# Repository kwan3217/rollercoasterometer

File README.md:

# rollercoasterometer
Rollercoasterometer

## kicad7 branch
This one is based on the Shipometer 23.03, but updated to KiCad 7.0. There are initially no other changes.

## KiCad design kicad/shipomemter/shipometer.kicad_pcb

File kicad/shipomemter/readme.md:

# Shipometer
The *Shipometer* is designed to record as much data as possible on a cruise
ship. To this end, it is composed of a Raspberry Pi running Raspbian, along
with several other programs, and both off-the-shelf and custom hardware.

Sensors include:

* ADS-B radio for recording flight information
* AIS radio for recording ship logs
* GPS for own position and timing
* Inertial measurement unit because we can
* Pressure, temperature, and humidity sensor because it's interesting
* Magnetometer, which will be challenging to use on a steel ship
* Logging of on-chip die temperature, clock frequency, and load.

This folder documents the Shipometer HAT, which holds a socket for a Sparkfun
ZED-F9R breakout GPS. This part has its own inertial sensor and GPS receiver,
as well as a serial data stream and an accurate PPS signal.

We also include sockets for what I call *stamps* (based on their appearance
with castellated edges). The stamps take up much less space than a full breakout
board, but at the same time can be independently assembled and tested. I have
in mind the wild idea of a whole series of stamps, all with roughly compatible
pinouts. So far I have designed two, one which supports a BME280 
pressure/temperature/humidity sensor, and one which supports an ICM20948 9DoF
sensor.

The hat itself includes an LPC2102 microcontroller, used as a timer. It is able
to record the time of each PPS to within one 60MHz clock cycle, and is also
hooked up to time the data-ready outputs of the inertial and pressure stamp.

It also includes hardware to multiplex the chip select lines (so that all chips
can be read in SPI mode) and a 1.8V regulator, both to supply power to the timer
and to the inertial sensor.

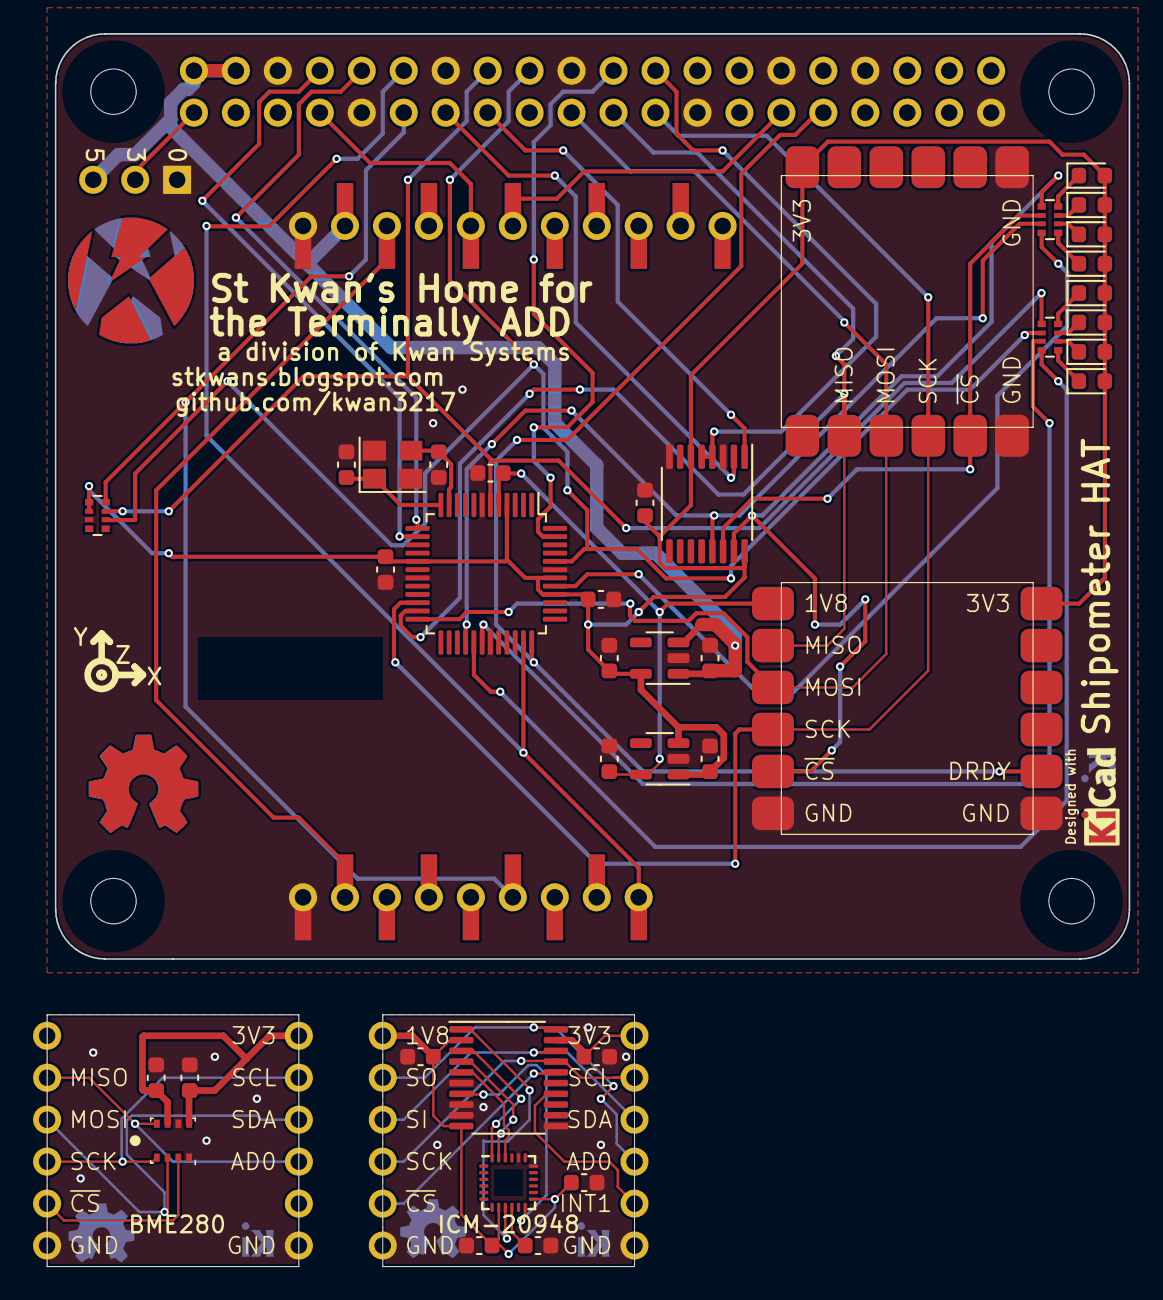
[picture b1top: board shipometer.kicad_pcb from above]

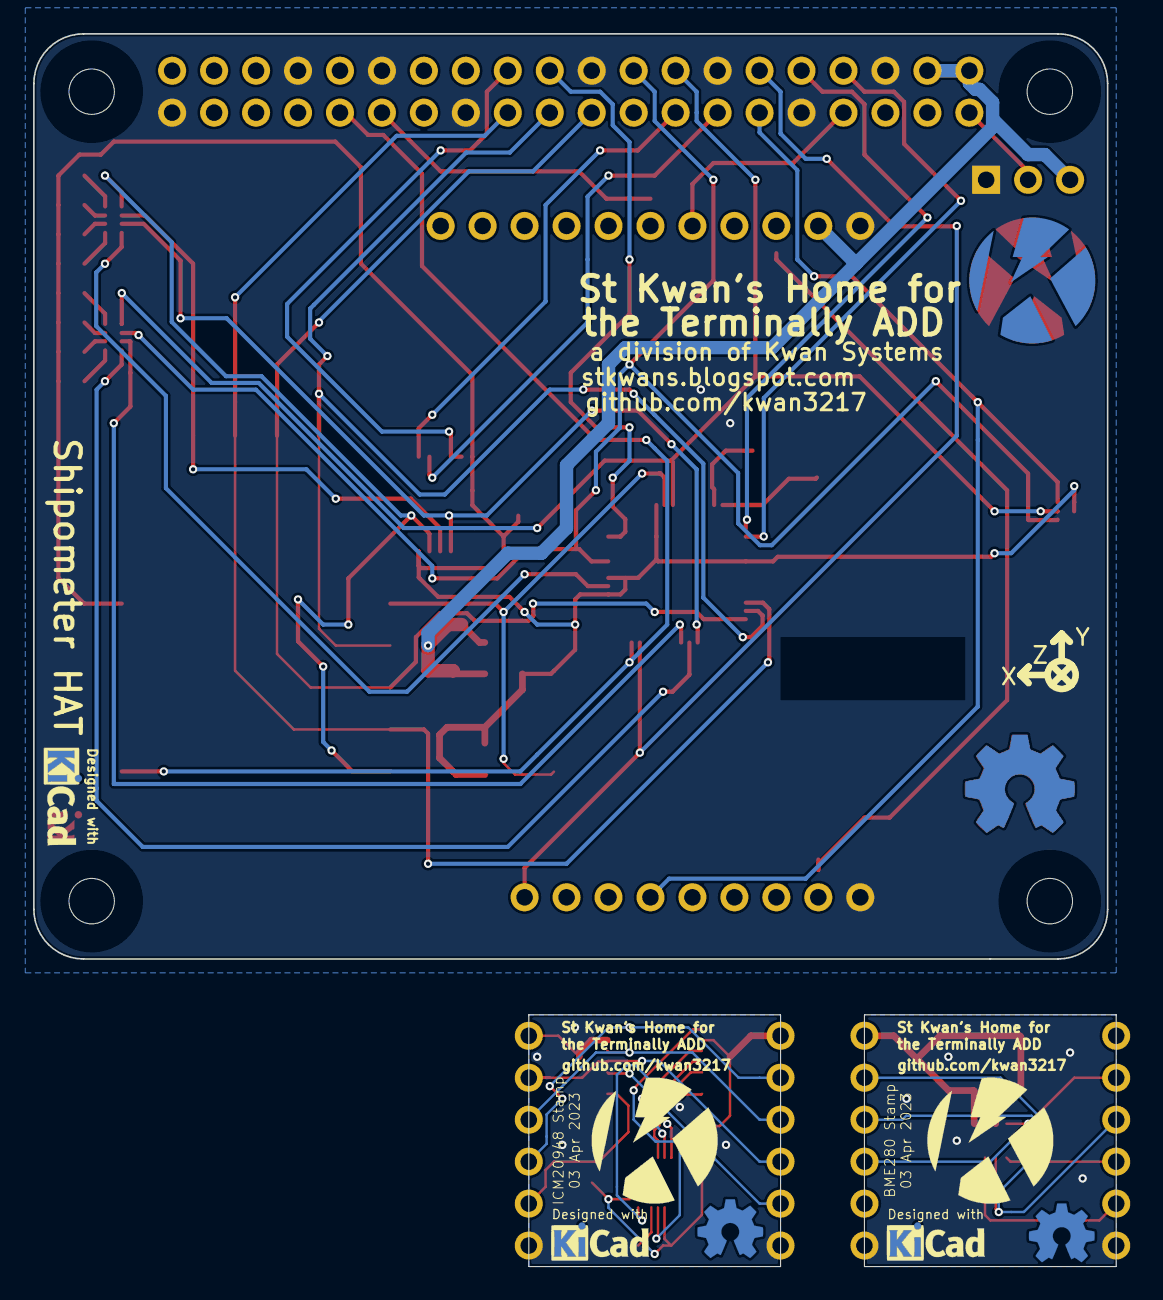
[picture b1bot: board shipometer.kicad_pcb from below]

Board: 2 copper layers, 65.5 x 74.6 mm, 56 parts (9 on the bottom side), 58 nets.

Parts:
C116, C206, C208, C401, C405, C501, C505, C605, C617, C640: 1uF; C_0603_1608Metric
C302, C308, C310, C313, C319: 100nF; C_0603_1608Metric
C611, C612: 22pF; C_0603_1608Metric
D101, D103, D104: White; LED_0603_1608Metric
D106: Blue; LED_0603_1608Metric
D129: Red; LED_0603_1608Metric
D130: Green; LED_0603_1608Metric
D141, D144: Yellow; LED_0603_1608Metric
G101: Axis
G102, G105: KwanSystems; StKwansSoldermask
G103, G107, G202, G302: Designed with; Symbol_KiCAD-Logo_CopperAndSilkScreenTop_small
G104, G106: OSHW; OSHW-Symbol_6.7x6mm_SolderMask
G201, G301: github.com/kwan3217; KWAN_CIRCLE
G203, G303: OSHW; OSHW-Symbol_4x3.6mm_SolderMask
J101: Raspberry_Pi_40; PiHAT_NoSlot_Narrow
J102: Conn_01x03; PinHeader_1x03_P2.54mm_Horizontal
J104: ICM20948; StampPad
J105: BME280; StampPad
J106: ZED-F9R
J201, J301: Stamp
R101, R102: 330; R_Array_Convex_4x0402
R103: 10k; R_Array_Convex_4x0402
U102: 74LS138; TSSOP-16_4.4x5mm_P0.65mm
U201: BME280; Bosch_LGA-8_2.5x2.5mm_P0.65mm_ClockwisePinNumbering
U301: ICM-20948; InvenSense_QFN-24_3x3mm_P0.4mm
U302: TXS0108EPW; TSSOP-20_4.4x6.5mm_P0.65mm
U401: TCR2EF 3.3V; SOT-23-5
U501: TCR2EF 1.8V; SOT-23-5
U601: LPC210x; LQFP-48_7x7mm_P0.5mm
Y601: 12MHz; Crystal_SMD_Abracon_ABM8G-4Pin_3.2x2.5mm

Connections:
3V3: J106.3 (3V3), J106.13 (3V3)
+1V8: C505.1, C605.1, J104.1 (1V8), U501.5 (OUT), U601.5 (VDD(1V8))
+3.3VP: J101.1 (3V3), J102.2
+3V3: C116.1, C405.1, C501.1, C617.1, C640.1, D101.2 (A), D103.2 (A), D104.2 (A), D106.2 (A), D129.2 (A), D130.2 (A), D141.2 (A), D144.2 (A), J104.12 (3V3), J105.12 (3V3), R103.1 (4), R103.2 (4), U102.6 (E3), U102.16 (VCC), U401.5 (OUT), U501.1 (IN), U501.3 (EN), U601.4 (VBAT), U601.17 (VDD(3V3)), U601.40 (VDD(3V3)), U601.42 (VDDA)
+5V: C401.1, J101.2 (5V), J101.4 (5V), J102.3, J106.2 (5V), U401.1 (IN), U401.3 (EN)
/BOOTSTRAP-: D144.1 (K), R102.7 (5)
/CS_A0: J101.15 (GPIO22_(GEN3)), U102.1 (A0)
/CS_A1: J101.13 (GPIO27_(GEN2)), U102.2 (A1)
/DRDY-: D129.1 (K), R102.5
/DRDY_6D: J101.31 (GPIO6), J104.8 (DRDY), U601.36 ((CTS1/CAP1.1/AD0.4)P0.11)
/DRDY_MAG: J101.22 (GPIO25_(GEN6)), U601.47 ((CAP1.2/SCL1)P0.17)
/DRDY_MAG-: D130.1 (K), R102.6 (5)
/GPS_RX: J101.7 ((TX3)_GPIO4), J106.5 (RX/MOSI)
/GPS_TX: J101.29 ((RX3)_GPIO5), J106.6 (TX/MISO)
/GPS_~RESET: J101.11 (GPIO17_(GEN0)), J106.17 (~RESET), R103.8 (5)
/IMU/INT1_1V8: U301.12 (INT1), U302.7 (A6)
/IMU/INT1_3V3: J301.8 (INT1), U302.14 (B6)
/IMU/MISO_1V8: U301.9 (SDO/AD0), U302.1 (A1)
/IMU/MISO_3V3: J301.2 (MISO), J301.9 (AD0), U302.20 (B1)
/IMU/MOSI_1V8: U301.24 (SDA/SDI), U302.3 (A2)
/IMU/MOSI_3V3: J301.3 (MOSI), J301.10 (SDA), U302.18 (B2)
/IMU/Q_1V8: C302.1, C308.1, C313.1, J301.1 (1V8), U301.8 (VDDIO), U301.13 (VDD), U302.2 (VCCA), U302.10 (OE)
/IMU/Q_3V3: C319.1, J301.12 (3V3), U302.19 (VCCB)
/IMU/Q_GND: C302.2, C308.2, C310.2, C313.2, C319.2, J301.6 (GND), J301.7 (GND), U301.18 (GND), U301.20 (GND), U302.6 (A5), U302.8 (A7), U302.9 (A8), U302.11 (GND)
/IMU/SCK_1V8: U301.23 (SCL/SCLK), U302.4 (A3)
/IMU/SCK_3V3: J301.4 (SCK), J301.11 (SCL), U302.17 (B3)
/IMU/~CS_1V8: U301.22 (~CS), U302.5 (A4)
/IMU/~CS_3V3: J301.5 (~CS), U302.16 (B4)
/LPC_RESET-: D106.1 (K), R102.8 (5)
/LPC_RX: J101.8 ((TX0)_GPIO14), U601.14 ((RXD0/MAT3.2)P0.1)
/LPC_TX: J101.10 ((RX0)_GPIO15), U601.13 ((TXD0/MAT3.1)P0.0)
/LPC_~BOOTSTRAP: J101.18 (GPIO24_(GEN5)), R102.2 (4), R103.6 (5), U601.44 ((DCD1/SCK1/EINT1)P0.14)
/LPC_~RESET: J101.16 (GPIO23_(GEN4)), R102.1 (4), R103.7 (5), U601.6 (~RST)
/MISO_3V3: J101.21 ((SPI_MISO)_GPIO9), J104.2 (MISO), J105.2 (MISO), U601.23 ((MISO0/MAT0.1)P0.5)
/MOSI_3V3: J101.19 ((SPI_MOSI)_GPIO10), J104.3 (MOSI), J105.3 (MOSI), U601.24 ((MOSI0/CAP0.2)P0.6)
/PPS: J101.12 (GPIO18_(GEN1)), J106.20 (PPS), U601.35 ((RTS1/CAP1.0/AD0.3)P0.10)
/PPS-: D141.1 (K), R101.5
/Pressure/MISO: J201.2 (MISO), J201.9 (AD0), U201.5 (SDO)
/Pressure/MOSI: J201.3 (MOSI), J201.10 (SDA), U201.3 (SDI)
/Pressure/Q_3V3: C206.1, C208.1, J201.12 (3V3), U201.6 (VDDIO), U201.8 (VDD)
/Pressure/Q_GND: C206.2, C208.2, J201.6 (GND), J201.7 (GND), U201.1 (GND), U201.7 (GND)
/Pressure/SCK: J201.4 (SCK), J201.11 (SCL), U201.4 (SCK)
/Pressure/~CS: J201.5 (~CS), U201.2 (CSB)
/SCK_3V3: J101.23 ((SPI_SCLK)_GPIO11), J104.4 (SCK), J105.4 (SCK), U601.22 ((SCK0/CAP0.1)P0.4)
/Timer/XTAL1: C611.2, U601.11 (XTAL1), Y601.3
/Timer/XTAL2: C612.2, U601.12 (XTAL2), Y601.1
/~CE0: J101.24 ((~SPI_CE0)_GPIO8), U102.4 (E1), U102.5 (E2)
/~CS_6D: J104.5 (~CS), R101.1 (4), U102.15 (O0)
/~CS_6D+: D101.1 (K), R101.8 (5)
/~CS_LPC: R101.3 (4), U102.13 (O2), U601.28 ((SSEL0/MAT2.0)P0.7)
/~CS_LPC+: D104.1 (K), R101.6 (5)
/~CS_PRES: J105.5 (~CS), R101.2 (4), U102.14 (O1)
/~CS_PRES+: D103.1 (K), R101.7 (5)
/~DRDY_6D_ECHO: R102.4, U601.29 ((TXD1/MAT2.1)P0.8)
/~DRDY_MAG_ECHO: R102.3 (4), U601.30 ((RXD1/MAT2.2)P0.9)
/~PPS_ECHO: R101.4, U601.41 ((DTR1/MAT1.1)P0.13)
GND: C116.2, C401.2, C405.2, C501.2, C505.2, C605.2, C611.1, C612.1, C617.2, C640.2, J101.6 (GND), J101.9 (GND), J101.14 (GND), J101.20 (GND), J101.25 (GND), J101.30 (GND), J101.34 (GND), J101.39 (GND), J102.1, J104.6 (GND), J104.7 (GND), J105.6 (GND), J105.7 (GND), J106.1 (GND), J106.12 (GND), R103.3 (4), U102.3 (A2), U102.8 (GND), U401.2 (GND), U501.2 (GND), U601.7 (VSS), U601.19 (VSS), U601.31 (VSSA), U601.43 (VSS), Y601.2, Y601.4
unnamed: C310.1, U301.10 (REGOUT)

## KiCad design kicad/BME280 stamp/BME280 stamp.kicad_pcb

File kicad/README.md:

# Folder for Kicad source code for rollercoasterometer boards

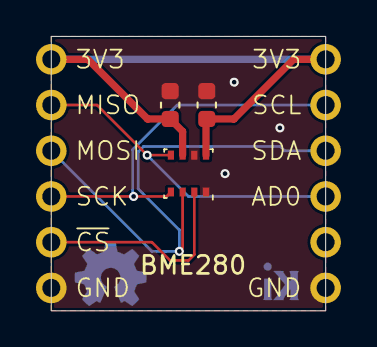
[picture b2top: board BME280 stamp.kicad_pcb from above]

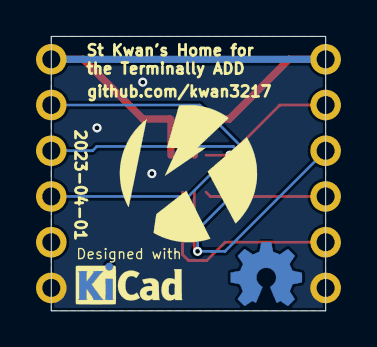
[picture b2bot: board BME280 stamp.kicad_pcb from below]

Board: 4 copper layers, 15.2 x 15.2 mm, 7 parts (3 on the bottom side), 6 nets.

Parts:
C506, C508: 100nF; C_0603_1608Metric
G1: github.com/kwan3217; KWAN_CIRCLE
G2: Designed with; Symbol_KiCAD-Logo_CopperAndSilkScreenTop_small
G3: OSHW; OSHW-Symbol_4x3.6mm_SolderMask
J501: Stamp
U501: BME280; Bosch_LGA-8_2.5x2.5mm_P0.65mm_ClockwisePinNumbering

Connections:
+3V3: C506.1, C508.1, J501.1 (3V3), J501.12 (3V3), U501.6 (VDDIO), U501.8 (VDD)
/MISO: J501.2 (MISO), J501.9 (AD0), U501.5 (SDO)
/MOSI: J501.3 (MOSI), J501.10 (SDA), U501.3 (SDI)
/SCK: J501.4 (SCK), J501.11 (SCL), U501.4 (SCK)
/~CS: J501.5 (~CS), U501.2 (CSB)
GND: C506.2, C508.2, J501.6 (GND), J501.7 (GND), U501.1 (GND), U501.7 (GND)

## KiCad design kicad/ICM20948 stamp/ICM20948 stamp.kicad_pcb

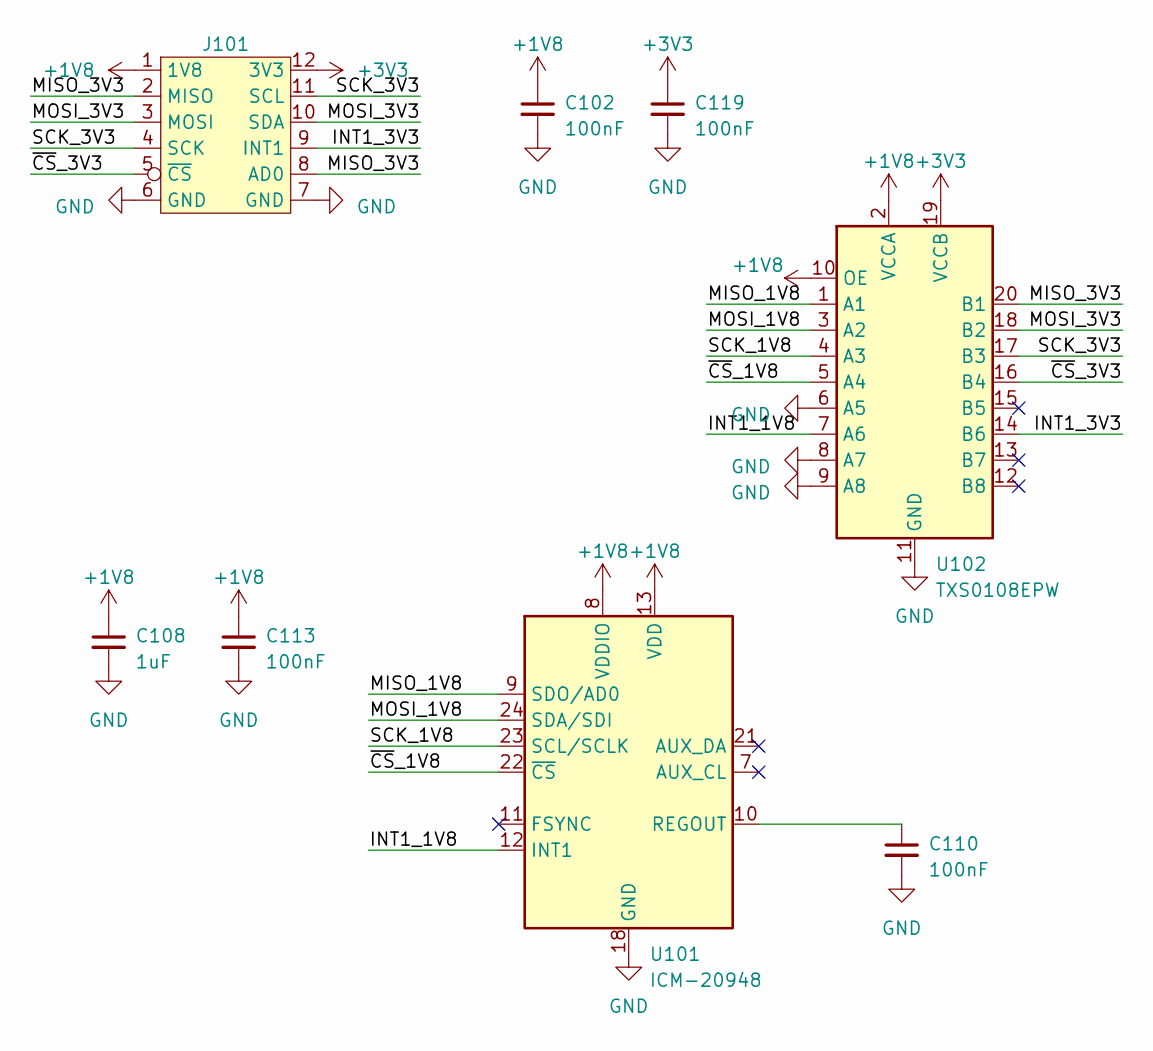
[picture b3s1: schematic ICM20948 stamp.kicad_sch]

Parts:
C102, C110, C113, C119: 100nF; C_0603_1608Metric
C108: 1uF; C_0603_1608Metric
J101: Stamp
U101: ICM-20948; InvenSense_QFN-24_3x3mm_P0.4mm
U102: TXS0108EPW; TSSOP-20_4.4x6.5mm_P0.65mm

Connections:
+1V8: C102.1, C108.1, C113.1, J101.1 (1V8), U101.8 (VDDIO), U101.13 (VDD), U102.2 (VCCA), U102.10 (OE)
+3V3: C119.1, J101.12 (3V3), U102.19 (VCCB)
/INT1_1V8: U101.12 (INT1), U102.7 (A6)
/INT1_3V3: J101.9 (INT1), U102.14 (B6)
/MISO_1V8: U101.9 (SDO/AD0), U102.1 (A1)
/MISO_3V3: J101.2 (MISO), J101.8 (AD0), U102.20 (B1)
/MOSI_1V8: U101.24 (SDA/SDI), U102.3 (A2)
/MOSI_3V3: J101.3 (MOSI), J101.10 (SDA), U102.18 (B2)
/SCK_1V8: U101.23 (SCL/SCLK), U102.4 (A3)
/SCK_3V3: J101.4 (SCK), J101.11 (SCL), U102.17 (B3)
/~CS_1V8: U101.22 (~CS), U102.5 (A4)
/~CS_3V3: J101.5 (~CS), U102.16 (B4)
GND: C102.2, C108.2, C110.2, C113.2, C119.2, J101.6 (GND), J101.7 (GND), U101.18 (GND), U101.20 (GND), U102.6 (A5), U102.8 (A7), U102.9 (A8), U102.11 (GND)
unnamed: C110.1, U101.10 (REGOUT)

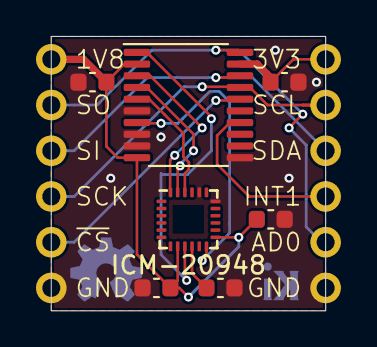
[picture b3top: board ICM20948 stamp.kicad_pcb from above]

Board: 4 copper layers, 15.2 x 15.2 mm, 8 parts (0 on the bottom side), 14 nets.

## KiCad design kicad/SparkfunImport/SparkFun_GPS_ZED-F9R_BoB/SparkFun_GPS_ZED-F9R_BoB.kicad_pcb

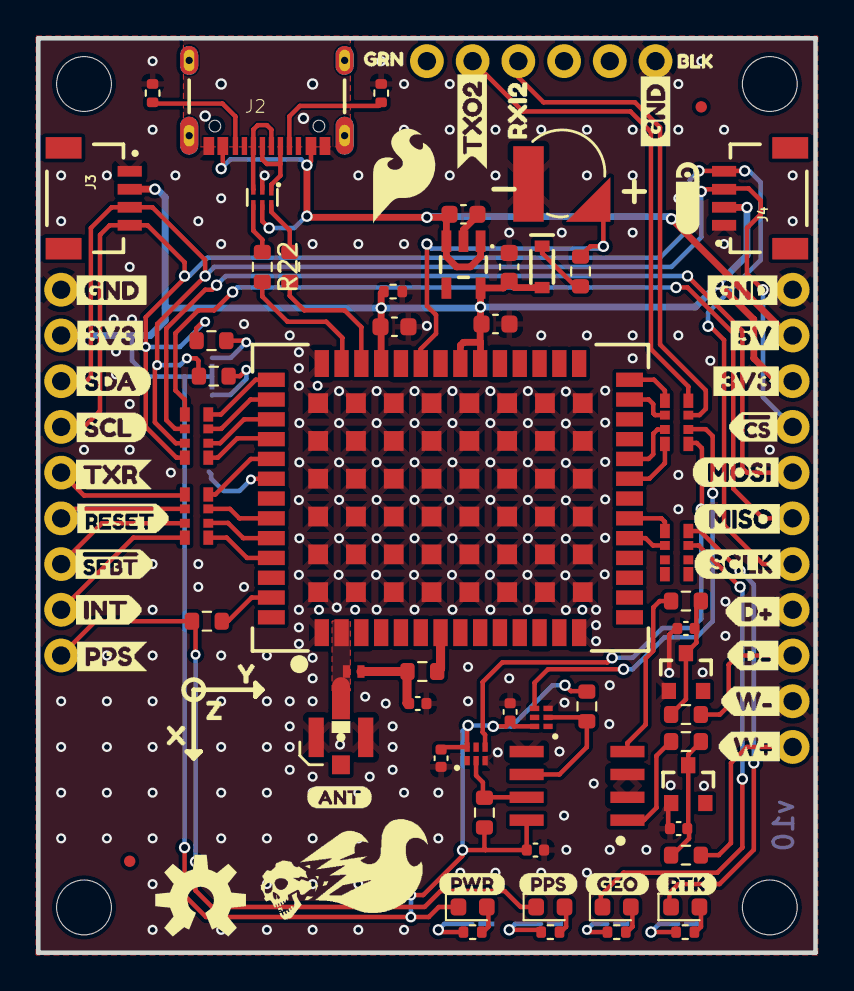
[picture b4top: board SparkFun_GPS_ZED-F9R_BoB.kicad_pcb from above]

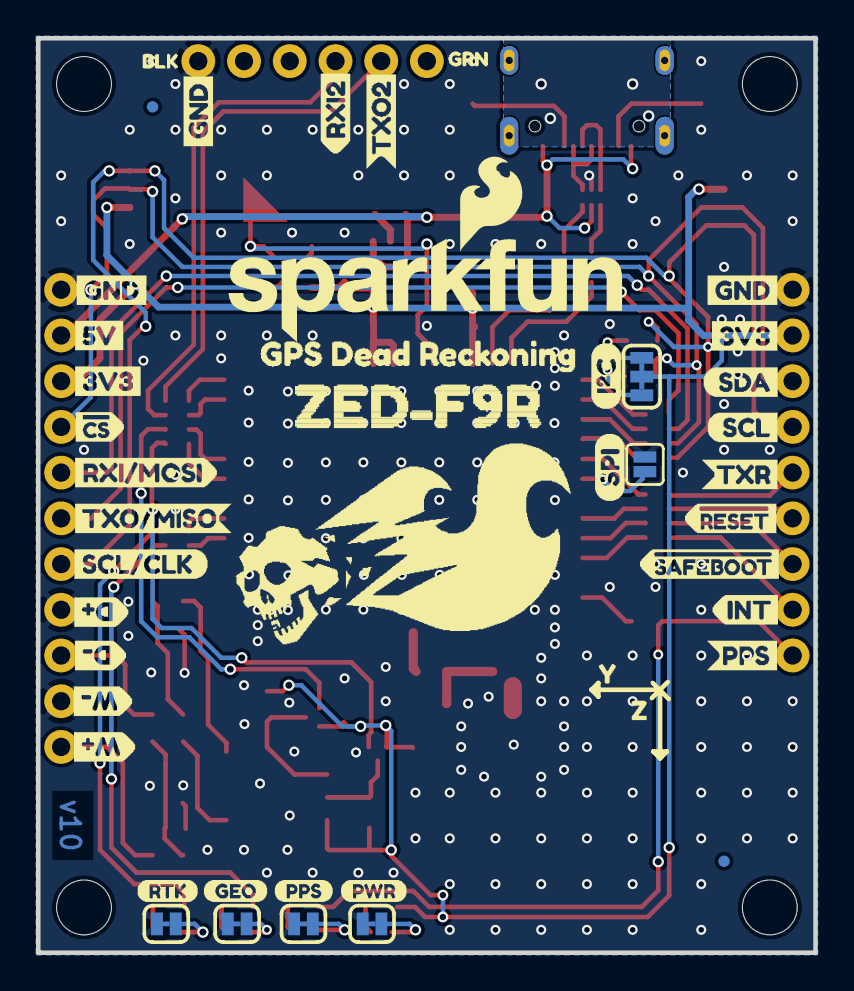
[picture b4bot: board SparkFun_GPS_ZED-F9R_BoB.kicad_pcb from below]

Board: 2 copper layers, 43.2 x 50.8 mm, 145 parts (45 on the bottom side), 60 nets.

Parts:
$1_25_$_2020-03-30_22-52-05: STAND-OFFTIGHT; STAND-OFF-TIGHT
BT1: ML414H_IV01E_BATTERY; ML414H_IV01E
C1, C6, C7: 0.1UF-0402-10V-10%-X7R; C_0402_1005Metric
C2, C5, C9, C10: 1.0UF-0603-16V-10%-X7R; C_0603_1608Metric
C3, C4: 1nF; C_0402_1005Metric
C8: 47PF-0402-25V-5%-X7R; C_0402_1005Metric
D1, D2: DIODE-ZENER-BZX84C15LT3G; SOT23-3
D3: PRTR5V0U2F; SOT886
D4: RED; LED_0603_1608Metric
D5, D6, D7: BLUE; LED_0603_1608Metric
D8: 0.5A/40V/420mV; SOD-323
FB1: FERRITE_BEAD_GNSS; 0402_MURATA
FD1, FD2, FD3, FD4: FIDUCIALUFIDUCIAL; FIDUCIAL-MICRO
FRAME1: FRAME-LEDGER; CREATIVE_COMMONS
H1, H2, H4: STAND-OFFTIGHT; STAND-OFF-TIGHT
J1: U.FL
J2: USB_C_2-LAYER_PADS; USB-C-16P-2LAYER-PADS
J3, J4: QWIIC_RIGHT_ANGLE; JST04_1MM_RA
J5: CONN_111X11_NO_SILK; 1X11_NO_SILK
J6: CONN_09NO_SILK; 1X09_NO_SILK
J7: CONN_06NO_SILK_NO_POP; 1X06_NO_SILK
JP1, JP2, JP3, JP4: JUMPER-SMT_2_NC_TRACE_SILK; SMT-JUMPER_2_NC_TRACE_SILK
JP5: JUMPER-SMT_2_NO_SILK; SMT-JUMPER_2_NO_SILK
JP6: JUMPER-SMT_3_2-NC_TRACE_SILK; SMT-JUMPER_3_2-NC_TRACE_SILK
LOGO1: OSHW-LOGOM; OSHW-LOGO-M
LOGO2: QWIIC_LOGO_4MM; QWIIC_4MM
LOGO3: SFE_LOGO_NAME_FLAME.2_INCH; SFE_LOGO_NAME_FLAME_.2
R1, R2, R24: 3.3KOHM-0603-1/10W-1%; R_0603_1608Metric
R3: 100KOHM-0402-1/16W-1%; R_0402_1005Metric
R4, R7: 910OHM-0603-1/10W-5%; R_0603_1608Metric
R5, R6: 470; R_0603_1608Metric
R8, R9, R10, R11: 33OHM_RA-1206-1/16W-5%; 1206_RA
R12, R13: 33OHM-0603-1/10W-1%; R_0603_1608Metric
R14, R15: 5.1k; R_0402_1005Metric
R16, R23: 2.2KOHM-0603-1/10W-1%; R_0603_1608Metric
R17, R18, R19, R20: 1KOHM-0402-1/16W-1%; R_0402_1005Metric
R21, R22: 27OHM-0603-1/10W-1%; R_0603_1608Metric
U1: DUAL-OPTO_HCPL-073L; SOP_8-PIN
U2: U-BLOX_ZED_F9R; UBLOX_ZED_F9R
U3, U4: UHS_INVERTER_SCHMITT_TRIGGERSIP6; SIP6
U5: V_REG_AP2112K-3.3V; SOT23-5
U$1, U$29, U$40, U$70: 3V3-04
U$2, U$15, U$31, U$34, U$41, U$71: GND-04
U$3, U$60: D#0
U$4, U$47: PPS8
U$5, U$48: PWR10
U$6, U$61: D#1
U$7: #RESET2
U$8, U$22: RTK9
U$9, U$64: W#2
U$10, U$65: W#3
U$11, U$33: 5V
U$12: INT1
U$13: PPS4
U$14: RXI22
U$16, U$36: TXO21
U$17: SCLK1
U$18: TXR0
U$19, U$20: DEAD#RECKONING#GPS#BOARD#SILK#FINAL#JPG
U$21, U$54: BLK2
U$23, U$53: GRN1
U$24: INT2
U$25: GPS_DEAD_RECKONING0
U$26: CS#-_]-04
U$27: PPS1
U$28: #SAFEBOOT3
U$30: RXI#MOSI0
U$32: X1
U$35: RXI28
U$37: TXO#MISO1
U$38: SCL#CLK2
U$39: SCL5
U$42: SDA4
U$43: TXR3
U$44: #RESET1
U$45: SPI4
U$46: I_SUPER2_C-()-04
U$49: ANT0
U$50, U$52: Y2
U$51: ZED#F9R0
U$55: #SFBT0
U$56, U$58: GEO1
U$57, U$63: Z0
U$59: CS#-[_-04
U$62: SFE_LOGO_FLAME_.2
U$66: MISO-(]-04
U$67: SCL-[)
U$68: SDA-[)
U$69: MOSI-(]-04

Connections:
3.3V: C1.1, C2.1, C5.1, C6.1, C7.1, C10.1, D8.A, J3.2, J4.2, J5.3, J6.8, JP6.2, R3.2, R4.2, R7.2, U1.P8 (VCC), U2.P33 (VCC), U2.P34 (VCC), U2.P38 (V_USB), U3.P6 (VCC), U4.P6 (VCC), U5.5 (OUT)
/SparkFun_GPS_ZED-F9R_BoB_1/DIR+: J5.9, R1.1
/SparkFun_GPS_ZED-F9R_BoB_1/DIR_IN: R5.2, U1.P4 (ANODE2)
/SparkFun_GPS_ZED-F9R_BoB_1/DIR_OUT: R10.P6 (2), U4.P4 (Y)
/SparkFun_GPS_ZED-F9R_BoB_1/DIR_SCHMITT: R4.1, U1.P6 (VOUT2), U4.P2 (A)
/SparkFun_GPS_ZED-F9R_BoB_1/DMINUS: R21.2, U2.P39 (USB_D-)
/SparkFun_GPS_ZED-F9R_BoB_1/DPLUS: R22.2, U2.P40 (USB_D+)
/SparkFun_GPS_ZED-F9R_BoB_1/D_SEL: JP5.1, U2.P47 (D_SEL)
/SparkFun_GPS_ZED-F9R_BoB_1/INT: J6.2, R8.P4 (1)
/SparkFun_GPS_ZED-F9R_BoB_1/PPS: J6.1, R12.2
/SparkFun_GPS_ZED-F9R_BoB_1/RF_IN: FB1.P1 (1), J1.FEED (SIGNAL), U2.P2 (RF_IN)
/SparkFun_GPS_ZED-F9R_BoB_1/RXI2: J7.4, R10.P7 (2)
/SparkFun_GPS_ZED-F9R_BoB_1/RXI/MOSI: J5.5, R9.P2 (1)
/SparkFun_GPS_ZED-F9R_BoB_1/SCL/CLK: J3.4, J4.4, J5.7, J6.6, R9.P4 (1), R16.1
/SparkFun_GPS_ZED-F9R_BoB_1/SDA/~CS: J3.3, J4.3, J5.4, J6.7, R9.P3 (1), R23.1
/SparkFun_GPS_ZED-F9R_BoB_1/SHIELD: J2.SHLD1 (SHLD), J2.SHLD2 (SHLD), J2.SHLD3 (SHLD), J2.SHLD4 (SHLD)
/SparkFun_GPS_ZED-F9R_BoB_1/TXO2: J7.5, R10.P8 (2)
/SparkFun_GPS_ZED-F9R_BoB_1/TXO/MISO: J5.6, R9.P1 (1)
/SparkFun_GPS_ZED-F9R_BoB_1/TX_READY: J6.5, R8.P1 (1)
/SparkFun_GPS_ZED-F9R_BoB_1/V_RF: R13.2, U2.P7 (V_RF)
/SparkFun_GPS_ZED-F9R_BoB_1/WT+: J5.11, R2.1
/SparkFun_GPS_ZED-F9R_BoB_1/WT_IN: R6.2, U1.P1 (ANODE1)
/SparkFun_GPS_ZED-F9R_BoB_1/WT_OUT: R10.P5 (2), U3.P4 (Y)
/SparkFun_GPS_ZED-F9R_BoB_1/WT_SCHMITT: R7.1, U1.P7 (VOUT1), U3.P2 (A)
/SparkFun_GPS_ZED-F9R_BoB_1/~RESET: J6.4, R8.P2 (1)
/SparkFun_GPS_ZED-F9R_BoB_1/~SAFEBOOT: J6.3, R8.P3 (1)
GND: BT1.-, C1.2, C2.2, C3.2, C4.2, C5.2, C6.2, C7.2, C8.2, C9.2, C10.2, D1.1 (A), D2.1 (A), D3.2, J1.1 (GND), J1.2 (GND), J2.GND, J2.GND2 (GND), J3.1, J4.1, J5.1, J5.8, J5.10, J6.9, J7.1, JP1.1, JP2.1, JP3.1, JP4.1, JP5.2, R3.1, R14.1, R15.1, U1.P2 (CATHODE1), U1.P3 (CATHODE2), U1.P5 (GND), U2.G1 (GND), U2.G2 (GND), U2.G3 (GND), U2.G4 (GND), U2.G5 (GND), U2.G6 (GND), U2.G7 (GND), U2.G8 (GND), U2.G9 (GND), U2.G10 (GND), U2.G11 (GND), U2.G12 (GND), U2.G13 (GND), U2.G14 (GND), U2.G15 (GND), U2.G16 (GND), U2.G17 (GND), U2.G18 (GND), U2.G19 (GND), U2.G20 (GND), U2.G21 (GND), U2.G22 (GND), U2.G23 (GND), U2.G24 (GND), U2.G25 (GND), U2.G26 (GND), U2.G27 (GND), U2.G28 (GND), U2.G29 (GND), U2.G30 (GND), U2.G31 (GND), U2.G32 (GND), U2.G33 (GND), U2.G34 (GND), U2.G35 (GND), U2.G36 (GND), U2.G37 (GND), U2.G38 (GND), U2.G39 (GND), U2.G40 (GND), U2.G41 (GND), U2.G42 (GND), U2.G43 (GND), U2.G44 (GND), U2.G45 (GND), U2.G46 (GND), U2.G47 (GND), U2.G48 (GND), U2.P1 (GND), U2.P3 (GND), U2.P12 (GND), U2.P14 (GND), U2.P32 (GND), U2.P37 (GND), U2.P41 (GND), U2.P48 (GND), U3.P3 (GND), U4.P3 (GND), U5.2 (GND)
unnamed: C3.1, D1.3 (C), R1.2, R5.1
unnamed: C4.1, D2.3 (C), R2.2, R6.1
unnamed: D3.1, J2.A7 (D-), J2.B7 (D-)
unnamed: D3.3, J2.A6 (D+), J2.B6 (D+)
unnamed: D3.4, R22.1
unnamed: D3.6, R21.1
unnamed: D8.C, R24.2
unnamed: C8.1, FB1.P2 (2), R13.1
unnamed: J2.A5 (CC1), R15.2
unnamed: J2.B5 (CC2), R14.2
unnamed: JP1.2, R17.1
unnamed: JP2.2, R18.1
unnamed: JP3.2, R19.1
unnamed: JP4.2, R20.1
unnamed: JP6.1, R23.2
unnamed: JP6.3, R16.2
unnamed: R8.P8 (2), U2.P46 (TX_READY)
unnamed: R8.P7 (2), U2.P49 (~RESET)
unnamed: R8.P6 (2), U2.P50 (~SAFEBOOT)
unnamed: R8.P5 (2), U2.P51 (EXTINT)
unnamed: R9.P8 (2), U2.P42 (TX/MISO)
unnamed: R9.P7 (2), U2.P43 (RX/MOSI)
unnamed: R9.P6 (2), U2.P44 (SDA/~CS)
unnamed: R9.P5 (2), U2.P45 (SCL/CLK)
unnamed: R10.P1 (1), U2.P27 (TX2)
unnamed: R10.P2 (1), U2.P26 (RX2)
unnamed: R10.P3 (1), U2.P23 (DIR)
unnamed: R10.P4 (1), U2.P22 (WHEEL_TKS)
unnamed: R11.P1 (1), U2.P20 (RTK_STAT)
unnamed: R11.P2 (1), U2.P19 (GEO_FENCE_STAT)
unnamed: R12.1, U2.P53 (TIMEPULSE)
VIN: C9.1, D3.5, J2.VBUS1 (VBUS), J2.VBUS2 (VBUS), J5.2, U5.1 (IN), U5.3 (EN)
V_BATT: BT1.+, R24.1, U2.P36 (V_BKCP)

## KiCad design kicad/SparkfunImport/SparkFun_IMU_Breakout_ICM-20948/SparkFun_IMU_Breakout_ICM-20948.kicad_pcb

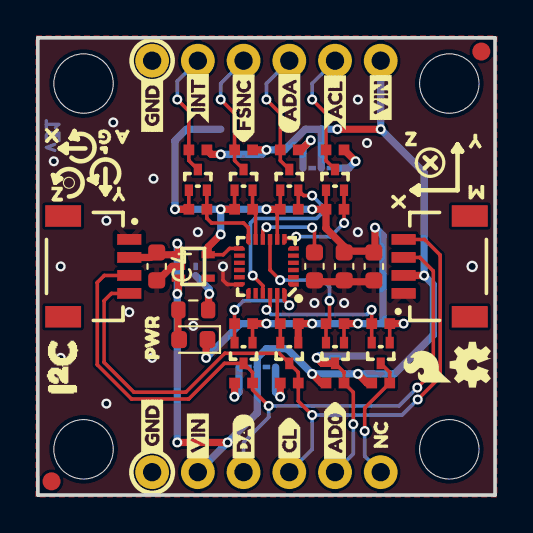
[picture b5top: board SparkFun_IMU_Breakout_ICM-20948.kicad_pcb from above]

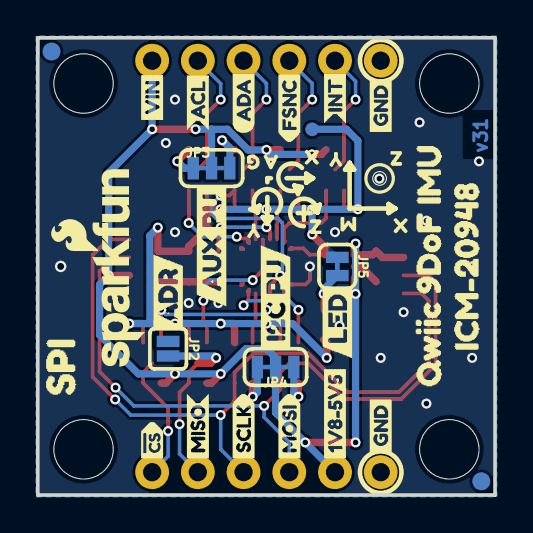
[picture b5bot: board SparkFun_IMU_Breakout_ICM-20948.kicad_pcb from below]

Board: 2 copper layers, 25.4 x 25.4 mm, 104 parts (36 on the bottom side), 25 nets.

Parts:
C1, C4: 1.0UF-0603-16V-10%-X7R; C_0603_1608Metric
C2, C3: 0.1UF-0603-25V-5%; C_0603_1608Metric
D1: RED; LED_0603_1608Metric
FD1, FD2, FD3, FD4: FIDUCIAL1X2; FIDUCIAL-1X2
FRAME2: FRAME-LEDGER; CREATIVE_COMMONS
H1, H2, H3, H4: STAND-OFF
J1, J2: QWIIC_CONNECTORJS-1MM; JST04_1MM_RA
J3, J4: CONN_06NO_SILK_NO_POP; 1X06_NO_SILK
JP2: JUMPER-SMT_2_NO_SILK; SMT-JUMPER_2_NO_SILK
JP3, JP4: JUMPER-SMT_3_2-NC_TRACE_SILK; SMT-JUMPER_3_2-NC_TRACE_SILK
JP5: JUMPER-SMT_2_NC_TRACE_SILK; SMT-JUMPER_2_NC_TRACE_SILK
LOGO1: SFE_LOGO_NAME_FLAME.1_INCH; SFE_LOGO_NAME_FLAME_.1
LOGO2: OSHW-LOGOMINI; OSHW-LOGO-MINI
Q2, Q4, Q6, Q8, Q10, Q12, Q14, Q16: MOSFET-NCH-RE1C002UN; SOT-416FL
R9: 220OHM-0603-1/10W-1%; R_0603_1608Metric
R10, R11, R12, R13, R14, R15, R16, R17, R18, R19, R20, R21, R22, R23, R24, R25: 2.2KOHM-0402T-1/16W-1%; 0402-TIGHT
TP1: TEST-POINT3; PAD.03X.03
U2: ICM-20948; QFN24-3X3
U3: V_REG_SP6214-1.8V; SC70
U$1, U$2, U$22, U$24: GND4
U$3: PWR0
U$4, U$21: INT3
U$5, U$20: FSNC2
U$6, U$19: ACL1
U$7, U$18: ADA0
U$8: MISO13
U$9: MOSI14
U$10: SCLK15
U$11: #CS16
U$12: 1V8#5V57
U$13, U$30, U$44: VIN5
U$14: NC17
U$15: CL4
U$16: DA2
U$17: AD012
U$23: ADR2
U$25: I2C_PU21
U$26: SPI19
U$27: AUX_PU24
U$28: SFE_LOGO_FLAME_.1
U$29: LED23
U$31: ICM#2094820
U$34, U$40, U$50, U$57: X0
U$35, U$41, U$51, U$58: Y1
U$36, U$42, U$52, U$59: Z2
U$37, U$60: G5
U$38, U$61: A4
U$39, U$49: M3
U$43: QWIIC_9DOF_IMU_0
U$45: I#C1

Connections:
1.8V: C1.1, C2.1, Q2.1 (G), Q4.1 (G), Q6.1 (G), Q8.1 (G), Q10.1 (G), Q12.1 (G), Q14.1 (G), Q16.1 (G), R10.2, R12.2, R14.2, R16.2, R18.2, R20.2, R22.2, R24.2, TP1.P$1 (1), U2.8 (VDDIO), U2.13 (VDD), U3.5 (OUT)
/AD0/SDO: Q4.2 (S), R12.1, U2.9 (AD0/SDO)
/AD0/SDO_VIN: J3.5, JP2.2, Q4.3 (D), R13.1
/AUX_CL: Q12.2 (S), R20.1, U2.7 (AUX_CL)
/AUX_CL_VIN: J4.5, Q12.3 (D), R21.1
/AUX_DA: Q10.2 (S), R18.1, U2.21 (AUX_DA)
/AUX_DA_VIN: J4.4, Q10.3 (D), R19.1
/FSYNC: Q14.2 (S), R22.1, U2.11 (FSYNC)
/FSYNC_VIN: J4.3, Q14.3 (D), R23.1
/INT: Q16.2 (S), R24.1, U2.12 (INT)
/INT_VIN: J4.2, Q16.3 (D), R25.1
/SCL/SCLK: Q6.2 (S), R14.1, U2.23 (SCL/SCLK)
/SCL/SCLK_VIN: J1.4, J2.4, J3.4, Q6.3 (D), R15.1
/SDA/SDI: Q8.2 (S), R16.1, U2.24 (SDA/SDI)
/SDA/SDI_VIN: J1.3, J2.3, J3.3, Q8.3 (D), R17.1
/~CS: Q2.2 (S), R10.1, U2.22 (~CS)
/~CS_VIN: J3.6, Q2.3 (D), R11.1
GND: C1.2, C2.2, C3.2, C4.2, J1.1, J2.1, J3.1, J4.1, JP2.1, JP5.1, U2.18 (GND), U2.20 (GND), U3.2 (GND)
unnamed: JP3.1, R21.2
unnamed: JP3.3, R19.2
unnamed: JP4.1, R17.2
unnamed: JP4.3, R15.2
unnamed: JP5.2, R9.1
unnamed: C3.1, U2.10 (REGOUT)
VIN: C4.1, J1.2, J2.2, J3.2, J4.6, JP3.2, JP4.2, R11.2, R13.2, R23.2, R25.2, U3.1 (IN), U3.3 (EN)

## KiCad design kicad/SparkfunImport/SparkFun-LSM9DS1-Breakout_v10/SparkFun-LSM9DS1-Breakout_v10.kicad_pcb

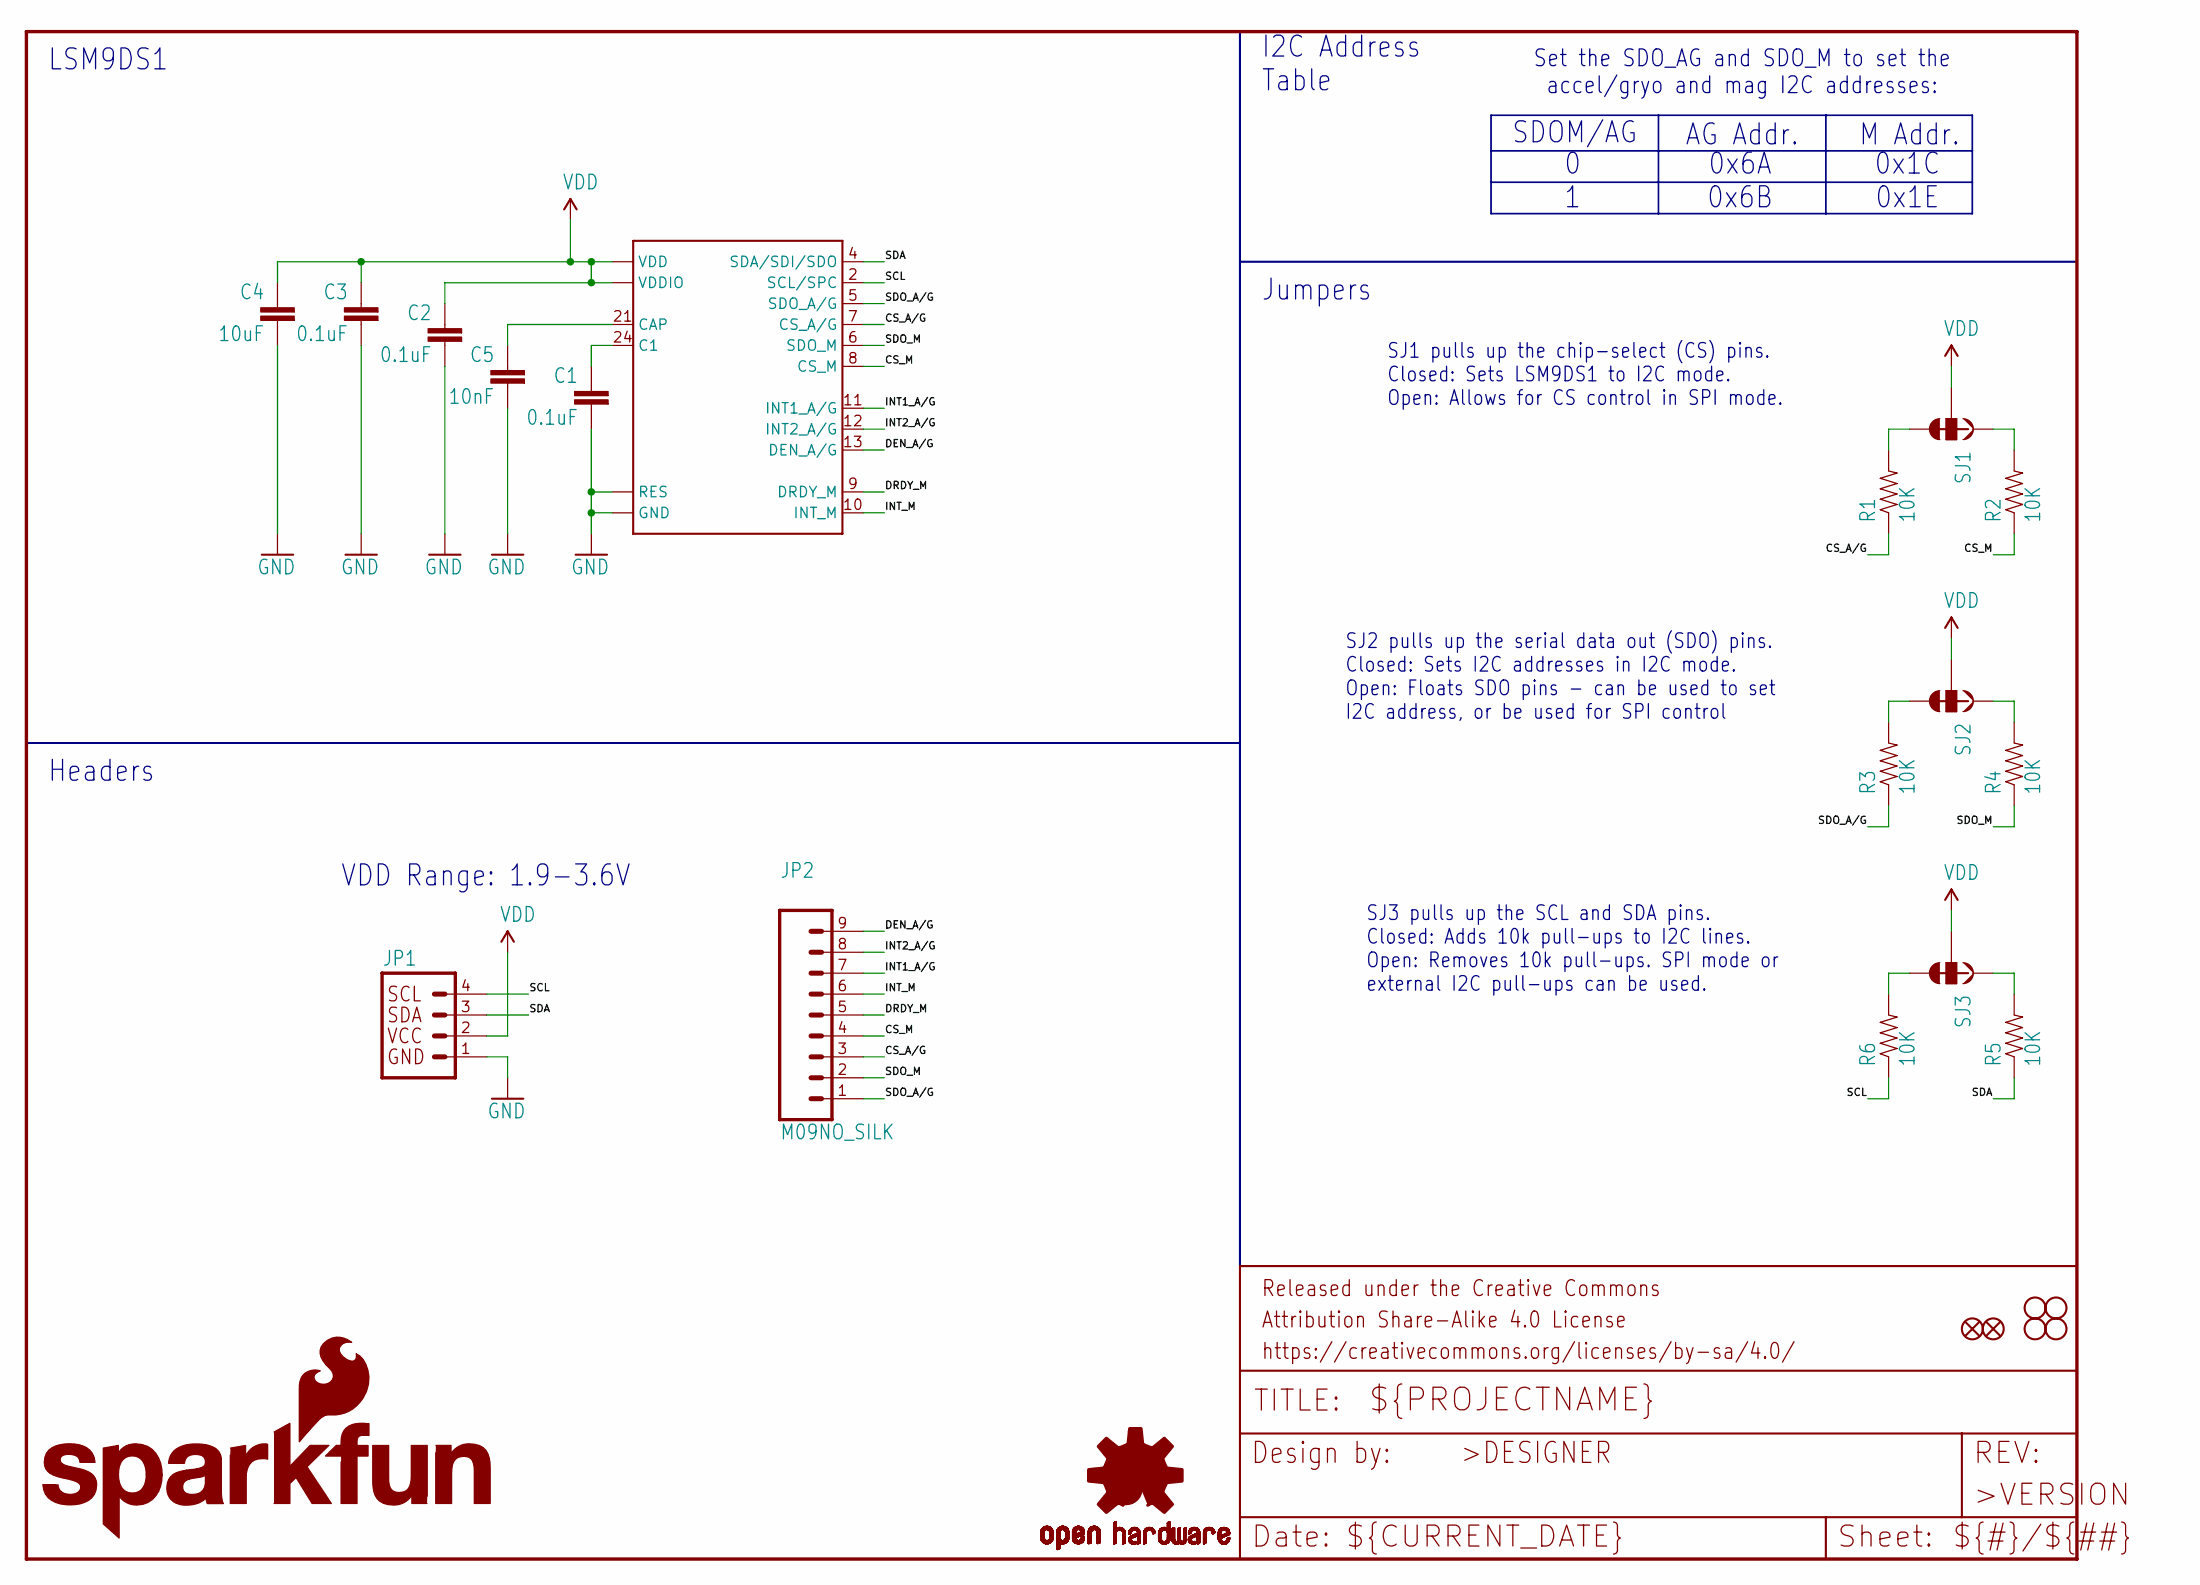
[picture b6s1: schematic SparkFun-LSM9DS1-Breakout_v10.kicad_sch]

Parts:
C1, C2, C3: 0.1uF; C_0603_1608Metric
C4: 10uF; C_0603_1608Metric
C5: 10nF; C_0603_1608Metric
FID1, FID2: FIDUCIAL1X2; FIDUCIAL-1X2
FRAME1: FRAME-LETTER; CREATIVE_COMMONS
JP1: I2C_STANDARD_NO_SILK; 1X04_NO_SILK
JP2: M09NO_SILK; 1X09_NO_SILK
LOGO1: SFE_LOGO_NAME.1_INCH; SFE_LOGO_NAME_.1
LOGO2: SFE_LOGO_FLAME.2_INCH; SFE_LOGO_FLAME_.2
LOGO3: OSHW-LOGOS; OSHW-LOGO-S
R1, R2, R3, R4, R5, R6: 10K; R_0603_1608Metric
SJ1, SJ2, SJ3: JUMPER-PAD-3-NC_BY_TRACE; PAD-JUMPER-3-3OF3_NC_BY_TRACE_YES_SILK_FULL_BOX
STANDOFF1, STANDOFF2, STANDOFF3, STANDOFF4: STAND-OFF
U1: LSM9DS1; LGA24-8X4

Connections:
/CS_A/G: JP2.3, R1.1, U1.7 (CS_A/G)
/CS_M: JP2.4, R2.1, U1.8 (CS_M)
/DEN_A/G: JP2.9, U1.13 (DEN_A/G)
/DRDY_M: JP2.5, U1.9 (DRDY_M)
/INT1_A/G: JP2.7, U1.11 (INT1_A/G)
/INT2_A/G: JP2.8, U1.12 (INT2_A/G)
/INT_M: JP2.6, U1.10 (INT_M)
/SCL: JP1.4, R6.1, U1.2 (SCL/SPC)
/SDA: JP1.3, R5.1, U1.4 (SDA/SDI/SDO)
/SDO_A/G: JP2.1, R3.1, U1.5 (SDO_A/G)
/SDO_M: JP2.2, R4.1, U1.6 (SDO_M)
GND: C1.2, C2.2, C3.2, C4.2, C5.2, JP1.1, U1.14 (RES), U1.15 (RES), U1.16 (RES), U1.17 (RES), U1.18 (RES), U1.19 (GND), U1.20 (GND)
unnamed: R1.2, SJ1.3
unnamed: R2.2, SJ1.1
unnamed: R3.2, SJ2.3
unnamed: R4.2, SJ2.1
unnamed: R5.2, SJ3.1
unnamed: R6.2, SJ3.3
unnamed: C1.1, U1.24 (C1)
unnamed: C5.1, U1.21 (CAP)
VDD: C2.1, C3.1, C4.1, JP1.2, SJ1.2, SJ2.2, SJ3.2, U1.1 (VDDIO), U1.3 (VDDIO), U1.22 (VDD), U1.23 (VDD)

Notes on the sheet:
Set the SDO_AG and SDO_M to set the accel/gryo and mag I2C addresses:
SJ1 pulls up the chip-select (CS) pins. Closed: Sets LSM9DS1 to I2C mode. Open: Allows for CS control in SPI mode.
SDOM/AG
0x1C 0x1E
SJ2 pulls up the serial data out (SDO) pins. Closed: Sets I2C addresses in I2C mode. Open: Floats SDO pins - can be used to set I2C address, or be used for SPI control
0x6A 0x6B
Jumpers
Headers
0 1
AG Addr.
SJ3 pulls up the SCL and SDA pins. Closed: Adds 10k pull-ups to I2C lines. Open: Removes 10k pull-ups. SPI mode or external I2C pull-ups can be used.
LSM9DS1
I2C Address Table
VDD Range: 1.9-3.6V
M Addr.

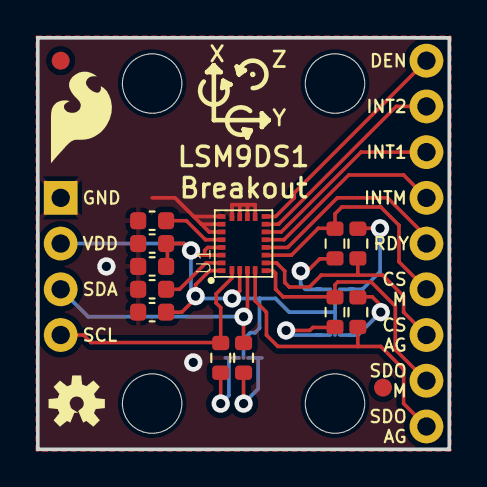
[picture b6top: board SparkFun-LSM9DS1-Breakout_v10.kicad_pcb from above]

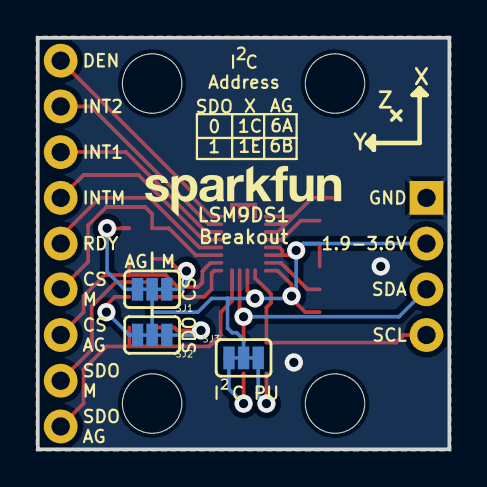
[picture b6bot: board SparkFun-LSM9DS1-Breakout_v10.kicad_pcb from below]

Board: 2 copper layers, 22.9 x 22.9 mm, 27 parts (4 on the bottom side), 21 nets.

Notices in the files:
kicad/SparkfunImport/Environmental_Sensor_Breakout_BME680/Environmental_Sensor_Breakout_BME680.kicad_sch:
https://creativecommons.org/licenses/by-sa/4.0
Released under the Creative Commons
parts and their libraries:
Released under the Creative Commons Attribution Share-Alike 4.0 License
